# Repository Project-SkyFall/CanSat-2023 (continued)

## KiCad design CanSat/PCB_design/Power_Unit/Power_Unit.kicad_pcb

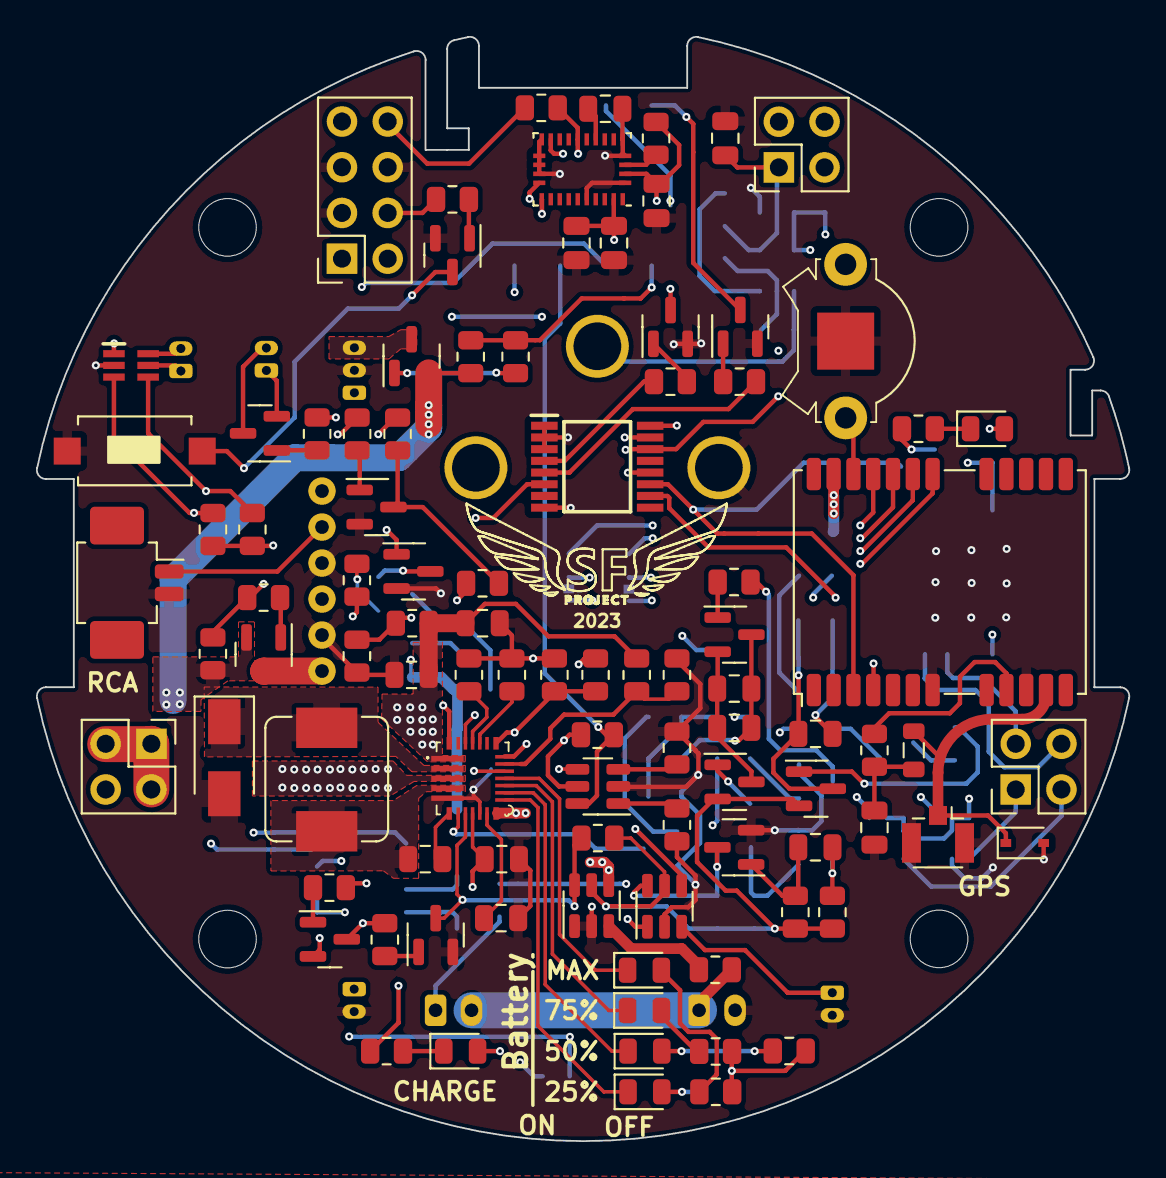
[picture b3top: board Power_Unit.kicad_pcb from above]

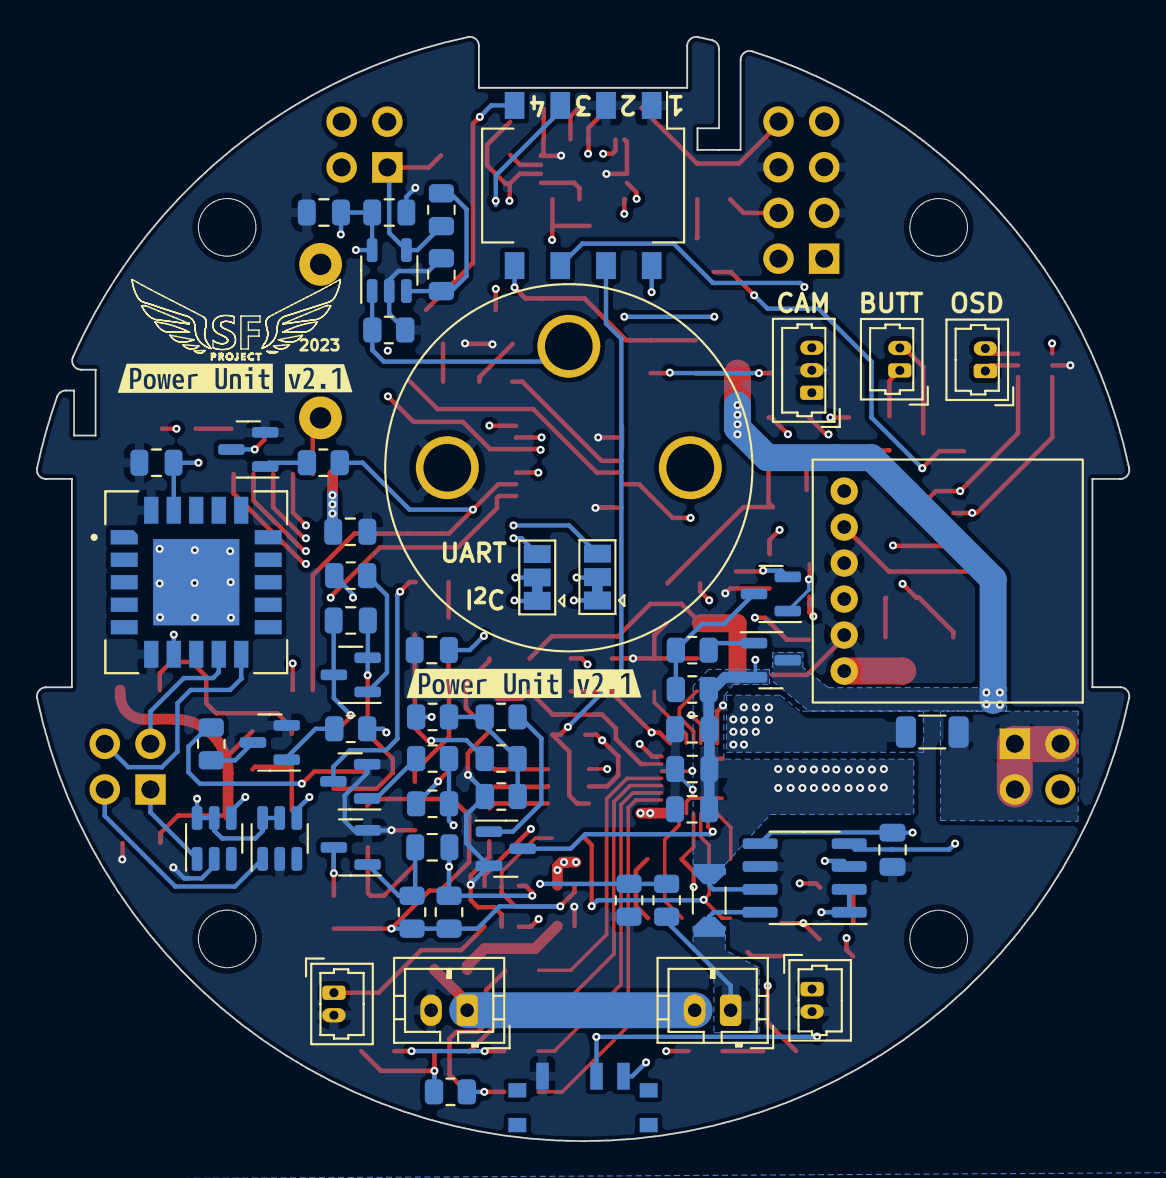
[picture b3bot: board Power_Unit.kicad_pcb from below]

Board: 4 copper layers, 60.7 x 61.3 mm, 162 parts (63 on the bottom side), 119 nets.

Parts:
AE1001: Antenna_Shield; U.FL_Hirose_U.FL-R-SMT-1_Vertical
BT301, BT302: Battery_Cell; JST_PH_B2B-PH-K_1x02_P2.00mm_Vertical
BT1001: Backup battery; 2989
C201, C401, C1102, C1204: 10uF; C_0805_2012Metric
C301, C302, C701, C702, C707, C1201, C1202: 22uF; C_0805_2012Metric
C703, C706, C1001: 1uF; C_0805_2012Metric
C704, C705, C803, C804, C901, C1002, C1101: 0.1uF; C_0805_2012Metric
C708: 4.7uF; C_0805_2012Metric
C801: 120nF; C_0805_2012Metric
C802: 6.8nF; C_0805_2012Metric
C1103: 10nF; C_0805_2012Metric
C1203: NC; C_0805_2012Metric
D701: B330A; D_SMA
D702, D703, D704, D705: APT2012LZGCK; LED_0805_2012Metric
D706: APT2012LSECK/J3-PRV; LED_0805_2012Metric
D1001: APT2012LSECK/J4-PRV; LED_0805_2012Metric
D1002: ESD7351HT1G; D_SOD-323
H201, H202, H203, H204: MountingHole; MountingHole_3.2mm_M3
J101: Conn_02x04_Female; PinSocket_2x04_P2.54mm_Vertical
J102, J103, J104: Conn_02x02_Female; PinSocket_2x02_P2.54mm_Vertical
J501: Conn_01x02; Molex_PicoBlade_53261-0271_1x02-1MP_P1.25mm_Horizontal
J502: Conn_01x03; Molex_PicoBlade_53047-0310_1x03_P1.25mm_Vertical
J503, J504: Conn_01x02; Molex_PicoBlade_53047-0210_1x02_P1.25mm_Vertical
JP1001, JP1002: SolderJumper_3_Bridged12; SolderJumper-3_P1.3mm_Bridged12_Pad1.0x1.5mm
L701: SRP7050AA-2R2M; L_Bourns_SRP7050AA
L1001: 27nH; L_0805_2012Metric
Q201, Q202, Q203, Q207, Q209, Q210, Q211, Q212, Q301, Q302, Q501, Q1001, Q1202, Q1205: BC847; SOT-23
Q204, Q205, Q206: SI2305CDS-T1-BE3; SOT-23
Q208, Q1201, Q1203, Q1204, Q1206: BC857; SOT-23
R201, R202, R204, R207, R208, R209, R1201, R1202, R1203, R1204, R1205, R1206, R1209: 100k; R_0805_2012Metric
R203, R205, R206, R210, R214, R215, R220, R221, R222, R301, R304, R703, R716, R718, R801, R802, R1207: 10k; R_0805_2012Metric
R211: 12k; R_0805_2012Metric
R212, R216, R217, R218, R219, R501, R1001: 5k; R_0805_2012Metric
R213: 0R; R_1206_3216Metric
R302, R303: 220k; R_0805_2012Metric
R401: PE1206FRE470R04L; R_1206_Current
R701: 0R5; R_0805_2012Metric
R702: 3k16; R_0805_2012Metric
R704: 1k87; R_0805_2012Metric
R705: 1k3; R_0805_2012Metric
R706: 5k11; R_0805_2012Metric
R707, R708, R709, R710: 910R; R_0805_2012Metric
R712: 143k; R_0805_2012Metric
R713: 82k; R_0805_2012Metric
R714: 820k; R_0805_2012Metric
R715: 75k; R_0805_2012Metric
R717: 27k4; R_0805_2012Metric
R1002: 750R; R_0805_2012Metric
R1003: 10R; R_0805_2012Metric
R1101, R1102: 100R; R_0805_2012Metric
R1103: 20k; R_0805_2012Metric
R1208: 15k; R_0805_2012Metric
SW201: DS04-254-1-04BK-SMT; SW_DIP_SPSTx04_Slide_Omron_A6S-410x_W8.9mm_P2.54mm
SW202: PCM12SMTR
SW203: LaskaKit tlačítko; Tlačítko SMD LaskaKit
TH301, TH302: NRBE104J3435B2J; Molex_PicoBlade_53047-0210_1x02_P1.25mm_Vertical
U201: PCA8574PW; SOP65P640X110-16N
U301, U701, U703, U1002, U1003: TS5A3159DBV; SOT-23-6
U401: INA219AxD; SOIC-8_3.9x4.9mm_P1.27mm
U501: AD5246BKSZ100; SOT65P210X110-6N
U601: TBS_UNIFY_PRO32_5G8_nano; TBS UNIFY PRO32 5G8 nano
U702: MP2639AGR-Z; MP2639AGRZ
U801: BNO055; LGA-28_5.2x3.8mm_P0.5mm
U901: SCD41; XDCR_SCD41-D-R2
U1001: NEO-M9N; ublox_NEO
U1101: ME2-02; ME2-O2
U1102: MCP6486UT-E/OT; SOT-23-5
kibuzzard-63BEDE70, kibuzzard-63BEDE70#2: G***; kibuzzard-63BEDE70
kibuzzard-642811A6: G***; kibuzzard-642811A6
kibuzzard-642811B8: G***; kibuzzard-642811B8

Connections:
/Power Unit/BATT_INT: J101.4, R217.2
/Power Unit/BAT_SENSE: C201.1, J102.2, R211.2, R212.1
/Power Unit/Battery Pack/BAT_M: BT301.2 (-), BT302.1 (+), R701.2
/Power Unit/Battery Pack/NTC: R704.1, R706.1, U301.4, U702.20 (NTC)
/Power Unit/Battery Pack/NTC_SWITCH: C301.1, Q301.3 (C), R301.1, U301.6
/Power Unit/CAMTRANS-FET: Q204.2 (S), Q205.3 (D), Q206.2 (S), R208.2, R209.1
/Power Unit/CAM_CONTROL: R501.1, U201.6 (P2)
/Power Unit/CH_SLOW/FAST: R716.2, SW201.7, U703.6
/Power Unit/Camera transmit/VIDEO: J501.1, J502.1, U601.5 (Video)
/Power Unit/Camera transmit/V_IN: Q206.3 (D), U601.1 (V_{IN})
/Power Unit/Camera/V_IN: J502.3, Q204.3 (D)
/Power Unit/D delay/OUT: R220.2, R1207.2, R1208.2, R1209.2
/Power Unit/EXTINT_{GPS}: U201.10 (P5), U1001.4 (EXTINT)
/Power Unit/FPV_{SM_A}: J101.2, U601.6 (SA)
/Power Unit/GND: AE1001.2 (Shield), BT302.2 (-), BT1001.2 (-), C201.2, C401.1, C701.2, C702.2, C703.2, C705.2, C706.2, C707.2, C708.2, C801.2, C802.2, C803.2, C804.2, C901.2, C1001.1, C1002.1, C1101.2, C1102.2, C1103.2, D701.2 (A), D1002.2 (A), J101.3, J101.5, J101.6, J501.2, J502.2, Q201.2 (E), Q203.2 (E), Q207.2 (E), Q209.2 (E), Q210.2 (E), Q211.2 (E), Q212.2 (E), Q301.2 (E), Q302.2 (E), Q1001.2 (E), Q1202.2 (E), Q1205.2 (E), R212.2, R702.2, R706.2, R712.2, R713.2, R714.2, R715.2, R718.2, R1101.2, R1102.1, R1209.1, SW201.1, SW201.2, SW202.1 (A), SW203.1, TH301.2, TH302.2, U201.1 (A0), U201.2 (A1), U201.3 (A2), U201.8 (VSS), U301.2 (GND), U401.6 (GND), U501.2 (VSS), U601.2 (GND), U601.4 (GND), U701.1, U701.2 (GND), U702.5 (PGND), U702.10 (AGND), U703.2 (GND), U801.2 (GND), U801.5 (PS1), U801.6 (PS0), U801.15 (GNDIO), U801.16 (GNDIO), U801.17 (COM3), U801.18 (COM2), U801.25 (GNDIO), U901.6 (GND), U901.20 (GND), U901.21 (GND), U1001.7 (VDD_USB), U1001.10 (GND), U1002.2 (GND), U1003.2 (GND), U1101.1 (OUT-), U1102.2 (V-)
/Power Unit/IMU_{INT}: J102.4, U801.14 (INT)
/Power Unit/IS_CHARGE: Q208.3 (C), R201.1, R215.1
/Power Unit/IS_USB: J101.1, Q208.2 (E)
/Power Unit/M_SWITCH: J104.4, R204.1, R1201.1, R1202.1, R1205.1, R1206.1, SW202.2 (B)
/Power Unit/OXY_{OUT}: C1103.1, J102.1, R1103.2, U1102.4
/Power Unit/P_IN: BT301.1 (+), R211.1, R401.1, U401.8 (IN+)
/Power Unit/P_OUT: C701.1, C702.1, C703.1, Q205.2 (S), R202.2, R207.1, R401.2, U401.7 (IN-), U702.3 (VH)
/Power Unit/RESET_{IMU}: R802.2, U201.12 (P7), U801.11 (~RESET)
/Power Unit/SCL: J103.3, R221.2, U201.14 (SCL), U401.4 (SCL), U501.3 (SCL), U801.19 (COM1), U901.9 (SCL)
/Power Unit/SCL_{2}/TXD: J103.2, U1003.1
/Power Unit/SDA: J103.4, R222.2, U201.15 (SDA), U401.3 (SDA), U501.4 (SDA), U801.20 (COM0), U901.10 (SDA)
/Power Unit/SDA_{2}/RXD: J103.1, U1002.1
/Power Unit/SW_CAMERA: R206.2, R209.2, SW201.5
/Power Unit/SW_CAMERA_{IO}: R218.2, U201.4 (P0)
/Power Unit/SW_CHARGE: R216.1, SW201.8
/Power Unit/SW_TRANSMIT: R208.1, R210.1, SW201.6
/Power Unit/SW_TRANSMIT_{IO}: R219.2, U201.5 (P1)
/Power Unit/Switch-mode battery charger/BST: C704.2, U702.6 (BST)
/Power Unit/Switch-mode battery charger/FB: R702.1, R703.2, U702.17 (FB)
/Power Unit/Switch-mode battery charger/ILIM: U702.24 (ILIM), U703.4
/Power Unit/Switch-mode battery charger/ISET: R712.1, U702.23 (ISET)
/Power Unit/Switch-mode battery charger/LX: D701.1 (K), L701.2, U702.2 (LX)
/Power Unit/Switch-mode battery charger/MODE: Q207.3 (C), R214.2, U701.6, U702.8 (MODE)
/Power Unit/Switch-mode battery charger/OLIM: R715.1, U702.22 (OLIM)
/Power Unit/Switch-mode battery charger/SW: C704.1, L701.1, U702.4 (SW)
/Power Unit/Switch-mode battery charger/TMR: C705.1, U702.11 (TMR)
/Power Unit/Switch-mode battery charger/VL: C707.1, C708.1, R213.2, R703.1, R717.1, U702.1 (VL)
/Power Unit/Switch-mode battery charger/VLIM: R717.2, R718.1, U702.18 (VLIM)
/Power Unit/Switch-mode battery charger/VNTC: D706.2 (A), R704.2, R707.1, R708.1, R709.1, R710.1, U702.19 (VNTC)
/Power Unit/Switch-mode battery charger/~CHG: R705.2, U702.26 (~CHG)
/Power Unit/Switch-mode battery charger/~PB: Q209.3 (C), Q212.3 (C), SW203.2, U702.7 (~PB)
/Power Unit/TIMEPULSE_{GPS}: R1001.1, U201.11 (P6), U1001.3 (TIMEPULSE)
/Power Unit/VCC: C401.2, C801.1, C802.1, C803.1, C901.1, C1001.2, C1101.1, C1102.1, D1001.2 (A), J101.7, J101.8, J102.3, R221.1, R222.1, R801.2, R802.1, U201.16 (VDD), U401.1 (A1), U401.2 (A0), U401.5 (VS), U501.1 (VDD), U801.3 (VDD), U801.28 (VDDIO), U901.7 (VDD), U901.19 (VDDH), U1001.23 (VCC), U1002.5 (V+), U1002.6, U1003.5 (V+), U1003.6, U1102.5 (V+)
/Power Unit/VCC_5V: J104.1, J104.2, J104.3, R213.1
/Power Unit/VCC_{BCK}: C706.1, Q1201.2 (E), Q1204.2 (E), R214.1, R301.2, R302.2, R303.2, R304.2, R716.1, SW202.3 (C), U301.5 (V+), U701.5 (V+), U702.9 (VCC), U703.5 (V+)
unnamed: AE1001.1 (A), D1002.1 (K), L1001.2, U1001.11 (RF_IN)
unnamed: BT1001.1 (+), U1001.22 (V_BCKP)
unnamed: C301.2, Q302.1 (B), R302.1
unnamed: C302.1, Q301.1 (B), R303.1
unnamed: C302.2, Q302.3 (C), R304.1
unnamed: C804.1, U801.9 (CAP)
unnamed: C1002.2, L1001.1, R1003.1
unnamed: C1201.1, C1202.1, Q1201.3 (C), Q1203.2 (E)
unnamed: C1201.2, C1202.2, Q1203.3 (C), R1208.1
unnamed: C1203.1, C1204.1, Q1204.3 (C), Q1206.2 (E)
unnamed: C1203.2, C1204.2, Q1206.3 (C), R1207.1
unnamed: D702.1 (K), U702.13 (LED1)
unnamed: D702.2 (A), R710.2
unnamed: D703.1 (K), U702.14 (LED2)
unnamed: D703.2 (A), R707.2
unnamed: D704.1 (K), U702.15 (LED3)
unnamed: D704.2 (A), R708.2
unnamed: D705.1 (K), U702.16 (LED4)
unnamed: D705.2 (A), R709.2
unnamed: D706.1 (K), R705.1
unnamed: D1001.1 (K), R1002.1
unnamed: J503.1, Q501.2 (E)
unnamed: J503.2, Q501.3 (C)
unnamed: J504.1, U501.5 (B)
unnamed: J504.2, U501.6 (W)
unnamed: JP1001.1 (A), U1001.18 (SDA/~SPI_CS)
unnamed: JP1001.2 (C), U1002.4
unnamed: JP1001.3 (B), U1001.20 (TXD/SPI_MISO)
unnamed: JP1002.1 (A), U1001.19 (SCL/SPI_CLK)
unnamed: JP1002.2 (C), U1003.4
unnamed: JP1002.3 (B), U1001.21 (RXD/SPI_MOSI)
unnamed: Q201.1 (B), R201.2
unnamed: Q201.3 (C), R202.1, R203.1
unnamed: Q202.1 (B), R204.2
unnamed: Q202.2 (E), Q203.3 (C)
unnamed: Q202.3 (C), R205.2, R207.2
unnamed: Q203.1 (B), R203.2
unnamed: Q204.1 (G), R206.1
unnamed: Q205.1 (G), R205.1
unnamed: Q206.1 (G), R210.2
unnamed: Q207.1 (B), R215.2
unnamed: Q208.1 (B), R216.2
unnamed: Q209.1 (B), R217.1
unnamed: Q210.1 (B), R218.1
unnamed: Q210.3 (C), SW201.3
unnamed: Q211.1 (B), R219.1
unnamed: Q211.3 (C), SW201.4
unnamed: Q212.1 (B), R220.1
unnamed: Q501.1 (B), R501.2
unnamed: Q1001.1 (B), R1001.2
unnamed: Q1001.3 (C), R1002.2
unnamed: Q1201.1 (B), R1201.2
unnamed: Q1202.1 (B), R1202.2
unnamed: Q1202.3 (C), R1203.1
unnamed: Q1203.1 (B), R1203.2
unnamed: Q1204.1 (B), R1204.2
unnamed: Q1205.1 (B), R1205.2
unnamed: Q1205.3 (C), R1204.1
unnamed: Q1206.1 (B), R1206.2
unnamed: R701.1, U701.3
unnamed: R713.1, U703.3
unnamed: R714.1, U703.1
unnamed: R801.1, U801.4 (~BOOT_LOAD_PIN)
unnamed: R1003.2, U1001.9 (VCC_RF)
unnamed: R1101.1, U1101.2 (OUT), U1102.1 (+)
unnamed: R1102.2, R1103.1, U1102.3 (-)
unnamed: TH301.1, U301.1
unnamed: TH302.1, U301.3
unnamed: U701.4, U702.12 (MIND)

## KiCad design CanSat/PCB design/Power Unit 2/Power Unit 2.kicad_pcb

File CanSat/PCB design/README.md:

# PCB design
## Content
* ### [Disclaimer](#disclaimer-1)
* ### [Power Unit](#power-unit-1)

## Disclaimer
PCBs designed in KiCad

## Power Unit
### Description
Power Unit is base PCB from stackup. It charges batteries or supplies rest of CanSat with 5 V power.
### Used ICs
#### MP2639A
* Balances 2s Li-po batteries and charges them from USB
* Overvoltage, overcurrent and overtemperature battery protection
* Step-down battery voltage to 5 V

## Control Unit
### Description

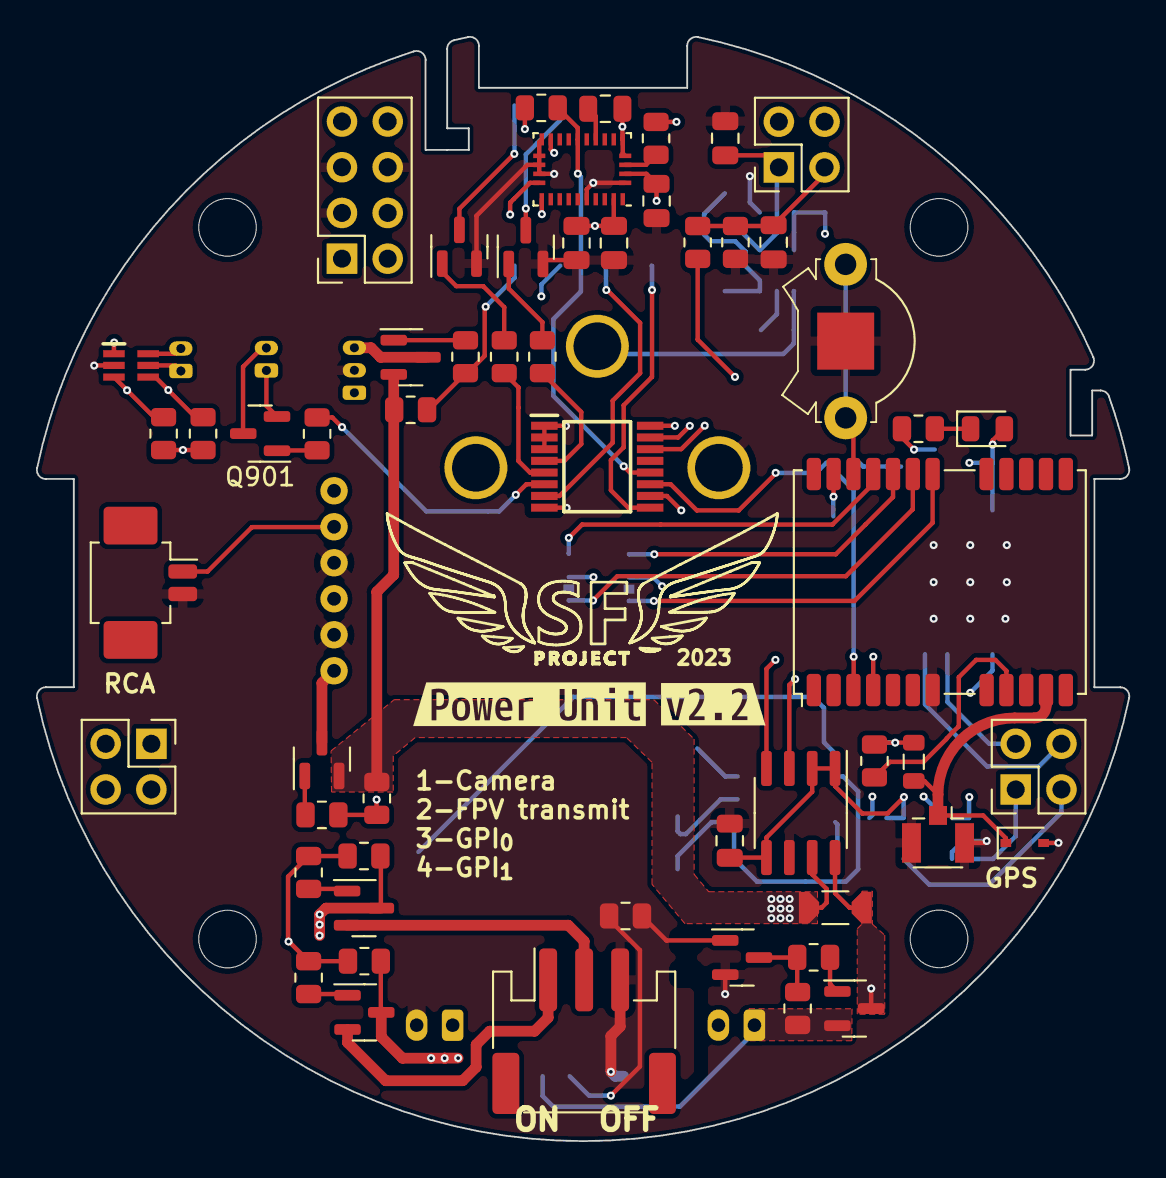
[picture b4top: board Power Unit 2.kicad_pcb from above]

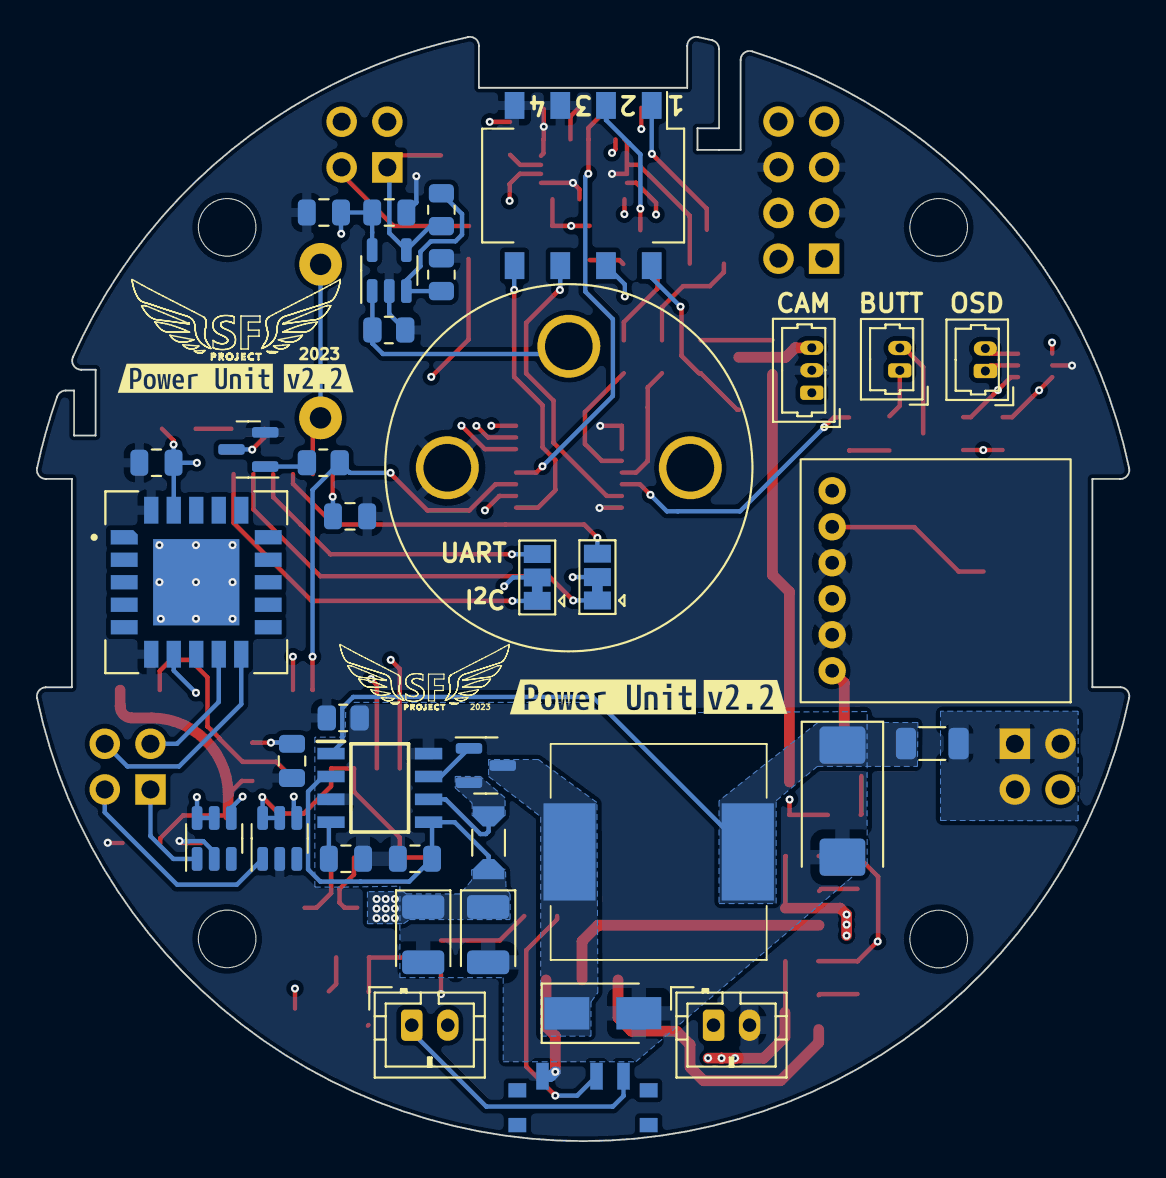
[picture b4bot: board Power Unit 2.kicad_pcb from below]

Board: 4 copper layers, 60.7 x 61.3 mm, 102 parts (41 on the bottom side), 70 nets.

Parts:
AE601: Antenna_Shield; U.FL_Hirose_U.FL-R-SMT-1_Vertical
BT201, BT202: Battery_Cell; JST_PH_B2B-PH-K_1x02_P2.00mm_Vertical
BT601: Backup battery; 2989
C201, C401, C802: 10uF; C_0805_2012Metric
C301, C503, C504, C602, C701, C801: 0.1uF; C_0805_2012Metric
C302, C303: TPSB686K010R0600; CP_EIA-3528-21_Kemet-B
C304: 0.47uF; C_0805_2012Metric
C305: 293D227X9010D2TE3; CP_EIA-7343-31_Kemet-D
C501: 120nF; C_0805_2012Metric
C502: 6.8nF; C_0805_2012Metric
C601: 1uF; C_0805_2012Metric
C803: 10nF; C_0805_2012Metric
D301: B330A; D_SMA
D601: APT2012LSECK/J4-PRV; LED_0805_2012Metric
D602: ESD7351HT1G; D_SOD-323
H201, H202, H203, H204: MountingHole; MountingHole_3.2mm_M3
IC301: MAX1626ESA+T; SOIC127P600X175-8N
J101: Conn_02x04_Female; PinSocket_2x04_P2.54mm_Vertical
J102, J103, J104: Conn_02x02_Female; PinSocket_2x02_P2.54mm_Vertical
J201: Conn_01x03; JST_PH_S3B-PH-SM4-TB_1x03-1MP_P2.00mm_Horizontal
J901: Conn_01x02; Molex_PicoBlade_53261-0271_1x02-1MP_P1.25mm_Horizontal
J902: Conn_01x03; Molex_PicoBlade_53047-0310_1x03_P1.25mm_Vertical
J903, J904: Conn_01x02; Molex_PicoBlade_53047-0210_1x02_P1.25mm_Vertical
JP601, JP602: SolderJumper_3_Bridged12; SolderJumper-3_P1.3mm_Bridged12_Pad1.0x1.5mm
L301: CDRH125NP-220MC; CDRH125101MC
L601: 27nH; L_0805_2012Metric
Q201, Q202, Q204, Q205, Q206, Q301: SI2305CDS-T1-BE3; SOT-23
Q203, Q207, Q208, Q601: BC847; SOT-23
Q901: BC857; SOT-23
R201, R202, R207, R210, R213, R218, R219, R501, R502: 10k; R_0805_2012Metric
R203, R204, R205, R206, R211, R212: 100k; R_0805_2012Metric
R208: 12k; R_0805_2012Metric
R209, R216, R217, R601, R901: 5k; R_0805_2012Metric
R214: 0R; R_0805_2012Metric
R215: 0R; R_1206_3216Metric
R301, R401: PE1206FRE470R04L; R_1206_Current
R602: 750R; R_0805_2012Metric
R603: 10R; R_0805_2012Metric
R801, R802: 100R; R_0805_2012Metric
R803: 20k; R_0805_2012Metric
SW201: DS04-254-1-04BK-SMT; SW_DIP_SPSTx04_Slide_Omron_A6S-410x_W8.9mm_P2.54mm
SW202: PCM12SMTR
U201: PCA8574PW; SOP65P640X110-16N
U401: INA219AxD; SOIC-8_3.9x4.9mm_P1.27mm
U501: BNO055; LGA-28_5.2x3.8mm_P0.5mm
U601, U602: TS5A3159DBV; SOT-23-6
U603: NEO-M9N; ublox_NEO
U701: SCD41; XDCR_SCD41-D-R2
U801: ME2-02; ME2-O2
U802: MCP6486UT-E/OT; SOT-23-5
U901: AD5246BKSZ100; SOT65P210X110-6N
U1001: TBS_UNIFY_PRO32_5G8_nano; TBS UNIFY PRO32 5G8 nano
kibuzzard-63BEDE70: G***; kibuzzard-63BEDE70
kibuzzard-642731D3: G***; kibuzzard-642731D3
kibuzzard-642753A9: G***; kibuzzard-642753A9
kibuzzard-642757A1: G***; kibuzzard-642757A1
kibuzzard-64275393: G***; kibuzzard-64275393
kibuzzard-64275791: G***; kibuzzard-64275791

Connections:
/Power Unit/BATT: BT201.1 (+), Q201.3 (D), Q204.2 (S), R203.2, R206.2, SW202.3 (C)
/Power Unit/BAT_SENSE: C201.1, J102.2, R208.2, R209.1
/Power Unit/CAMTRANS-FET: C302.1, C303.1, C304.1, IC301.2 (~_3/5), IC301.5 (V+), Q205.2 (S), Q206.2 (S), R211.2, R212.1, R301.1, R401.2, U401.7 (IN-)
/Power Unit/CAM_CONTROL: R901.1, U201.6 (P2)
/Power Unit/Camera transmit/VIDEO: J901.1, J902.1, U1001.5 (Video)
/Power Unit/Camera transmit/V_IN: Q206.3 (D), U1001.1 (V_{IN})
/Power Unit/Camera/V_IN: J902.3, Q205.3 (D)
/Power Unit/Current Sensor/P_IN: Q204.3 (D), R208.1, R401.1, U401.8 (IN+)
/Power Unit/EXTINT_{GPS}: U201.10 (P5), U603.4 (EXTINT)
/Power Unit/FPV_{SM_A}: J101.2, U1001.6 (SA)
/Power Unit/GND: AE601.2 (Shield), BT202.2 (-), BT601.2 (-), C201.2, C401.1, C501.2, C502.2, C503.2, C504.2, C601.1, C602.1, C701.2, C801.2, C802.2, C803.2, D602.2 (A), J101.3, J101.5, J101.6, J201.3, J901.2, J902.2, Q203.2 (E), Q207.2 (E), Q208.2 (E), Q601.2 (E), R209.2, R214.2, R801.2, R802.1, SW201.3, SW201.4, SW202.1 (A), U201.1 (A0), U201.2 (A1), U201.3 (A2), U201.8 (VSS), U401.6 (GND), U501.2 (GND), U501.5 (PS1), U501.6 (PS0), U501.15 (GNDIO), U501.16 (GNDIO), U501.17 (COM3), U501.18 (COM2), U501.25 (GNDIO), U601.2 (GND), U602.2 (GND), U603.7 (VDD_USB), U603.10 (GND), U701.6 (GND), U701.20 (GND), U701.21 (GND), U801.1 (OUT-), U802.2 (V-), U901.2 (VSS), U1001.2 (GND), U1001.4 (GND)
/Power Unit/GPI_{0}: SW201.6, U201.7 (P3)
/Power Unit/GPI_{1}: SW201.5, U201.9 (P4)
/Power Unit/IMU_{INT}: J102.4, U501.14 (INT)
/Power Unit/M_SWITCH: J104.4, R201.1, R202.1, R203.1, R204.1, R205.1, SW202.2 (B)
/Power Unit/OXY_{OUT}: C803.1, J102.1, R803.2, U802.4
/Power Unit/RESET_{IMU}: R502.2, U201.12 (P7), U501.11 (~RESET)
/Power Unit/SCL: J103.3, R218.2, U201.14 (SCL), U401.4 (SCL), U501.19 (COM1), U701.9 (SCL), U901.3 (SCL)
/Power Unit/SCL_{2}/TXD: J103.2, U602.1
/Power Unit/SDA: J103.4, R219.2, U201.15 (SDA), U401.3 (SDA), U501.20 (COM0), U701.10 (SDA), U901.4 (SDA)
/Power Unit/SDA_{2}/RXD: J103.1, U601.1
/Power Unit/SW_CAMERA: R210.2, R212.2, SW201.8
/Power Unit/SW_CAMERA_{IO}: R217.2, U201.5 (P1)
/Power Unit/SW_TRANSMIT: R211.1, R213.1, SW201.7
/Power Unit/SW_TRANSMIT_{IO}: R216.2, U201.4 (P0)
/Power Unit/Step-down/GND: C301.2, C302.2, C303.2, C304.2, C305.2, D301.2 (A), IC301.3 (SHDN), IC301.8 (GND), R214.1
/Power Unit/Step-down/L_MOSFET: IC301.6 (CS), Q301.2 (S), R301.2
/Power Unit/Step-down/L_{SWITCH}: D301.1 (K), L301.1, Q301.3 (D)
/Power Unit/Step-down/VCC_5V: C305.1, IC301.1 (OUT), L301.2, R215.2
/Power Unit/TIMEPULSE_{GPS}: R601.1, U201.11 (P6), U603.3 (TIMEPULSE)
/Power Unit/VCC: C401.2, C501.1, C502.1, C503.1, C601.2, C701.1, C801.1, C802.1, D601.2 (A), J101.7, J101.8, J102.3, R218.1, R219.1, R501.2, R502.1, U201.16 (VDD), U401.1 (A1), U401.2 (A0), U401.5 (VS), U501.3 (VDD), U501.28 (VDDIO), U601.5 (V+), U601.6, U602.5 (V+), U602.6, U603.23 (VCC), U701.7 (VDD), U701.19 (VDDH), U802.5 (V+), U901.1 (VDD)
/Power Unit/VCC_5V: J104.1, J104.2, J104.3, R215.1
unnamed: AE601.1 (A), D602.1 (K), L601.2, U603.11 (RF_IN)
unnamed: BT201.2 (-), BT202.1 (+), Q202.3 (D), R204.2
unnamed: BT601.1 (+), U603.22 (V_BCKP)
unnamed: C301.1, IC301.4 (REF)
unnamed: C504.1, U501.9 (CAP)
unnamed: C602.2, L601.1, R603.1
unnamed: D601.1 (K), R602.1
unnamed: IC301.7 (EXT), Q301.1 (G)
unnamed: J201.1, Q201.2 (S)
unnamed: J201.2, Q202.2 (S)
unnamed: J904.1, U901.5 (B)
unnamed: J904.2, U901.6 (W)
unnamed: JP601.1 (A), U603.18 (SDA/~SPI_CS)
unnamed: JP601.2 (C), U601.4
unnamed: JP601.3 (B), U603.20 (TXD/SPI_MISO)
unnamed: JP602.1 (A), U603.19 (SCL/SPI_CLK)
unnamed: JP602.2 (C), U602.4
unnamed: JP602.3 (B), U603.21 (RXD/SPI_MOSI)
unnamed: Q201.1 (G), R201.2
unnamed: Q202.1 (G), R202.2
unnamed: Q203.1 (B), R205.2
unnamed: Q203.3 (C), R206.1, R207.2
unnamed: Q204.1 (G), R207.1
unnamed: Q205.1 (G), R210.1
unnamed: Q206.1 (G), R213.2
unnamed: Q207.1 (B), R216.1
unnamed: Q207.3 (C), SW201.2
unnamed: Q208.3 (C), SW201.1
unnamed: Q601.1 (B), R601.2
unnamed: Q601.3 (C), R602.2
unnamed: J903.1, Q901.2 (E)
unnamed: J903.2, Q901.3 (C)
unnamed: Q208.1 (B), R217.1
unnamed: R501.1, U501.4 (~BOOT_LOAD_PIN)
unnamed: R603.2, U603.9 (VCC_RF)
unnamed: R801.1, U801.2 (OUT), U802.1 (+)
unnamed: R802.2, R803.1, U802.3 (-)
unnamed: Q901.1 (B), R901.2

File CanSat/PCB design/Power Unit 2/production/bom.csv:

Designator,Footprint,Quantity,Value,LCSC Part #
AE601,U.FL_Hirose_U.FL-R-SMT-1_Vertical,1,Antenna_Shield,
"BT201, BT202",JST_PH_B2B-PH-K_1x02_P2.00mm_Vertical,2,Battery_Cell,
BT601,2989,1,Backup battery,
"C201, C401, C802",C_0805_2012Metric,3,10uF,
"C301, C503, C504, C602, C701, C801",C_0805_2012Metric,6,0.1uF,
"C302, C303",CP_EIA-3528-21_Kemet-B,2,TPSB686K010R0600,
C304,C_0805_2012Metric,1,0.47uF,
C305,CP_EIA-7343-31_Kemet-D,1,293D227X9010D2TE3,
C501,C_0805_2012Metric,1,120nF,
C502,C_0805_2012Metric,1,6.8nF,
C601,C_0805_2012Metric,1,1uF,
C803,C_0805_2012Metric,1,10nF,
D301,D_SMA,1,B330A,
D601,LED_0805_2012Metric,1,APT2012LSECK/J4-PRV,
D602,D_SOD-323,1,ESD7351HT1G,
IC301,SOIC127P600X175-8N,1,MAX1626ESA+T,
J101,PinSocket_2x04_P2.54mm_Vertical,1,Conn_02x04_Female,
"J102, J103, J104",PinSocket_2x02_P2.54mm_Vertical,3,Conn_02x02_Female,
J201,JST_PH_B3B-PH-SM4-TB_1x03-1MP_P2.00mm_Vertical,1,Conn_01x03,
J901,Molex_PicoBlade_53261-0271_1x02-1MP_P1.25mm_Horizontal,1,Conn_01x02,
J902,Molex_PicoBlade_53047-0310_1x03_P1.25mm_Vertical,1,Conn_01x03,
"J903, J904",Molex_PicoBlade_53047-0210_1x02_P1.25mm_Vertical,2,Conn_01x02,
"JP601, JP602",SolderJumper-3_P1.3mm_Bridged12_Pad1.0x1.5mm,2,SolderJumper_3_Bridged12,
L301,CDRH125101MC,1,CDRH125NP-220MC,
L601,L_0805_2012Metric,1,27nH,
"Q201, Q202, Q204, Q205, Q206, Q301",SOT-23,6,SI2305CDS-T1-BE3,
"Q203, Q207, Q208, Q601, Q901",SOT-23,5,BC847,
"R201, R202, R207, R210, R213, R218, R219, R501, R502",R_0805_2012Metric,9,10k,
"R203, R204, R205, R206, R211, R212",R_0805_2012Metric,6,100k,
R208,R_0805_2012Metric,1,12k,
"R209, R216, R217, R601, R901",R_0805_2012Metric,5,5k,
R214,R_0805_2012Metric,1,0R,
R215,R_1206_3216Metric,1,0R,
"R301, R401",R_1206_Current,2,PE1206FRE470R04L,
R602,R_0805_2012Metric,1,750R,
R603,R_0805_2012Metric,1,10R,
"R801, R802",R_0805_2012Metric,2,100R,
R803,R_0805_2012Metric,1,20k,
SW201,SW_DIP_SPSTx04_Slide_Omron_A6S-410x_W8.9mm_P2.54mm,1,DS04-254-1-04BK-SMT,
SW202,PCM12SMTR,1,PCM12SMTR,
U1001,TBS UNIFY PRO32 5G8 nano,1,TBS_UNIFY_PRO32_5G8_nano,
U201,SOP65P640X110-16N,1,PCA8574PW,
U401,SOIC-8_3.9x4.9mm_P1.27mm,1,INA219AxD,
U501,LGA-28_5.2x3.8mm_P0.5mm,1,BNO055,
"U601, U602",SOT-23-6,2,TS5A3159DBV,
U603,ublox_NEO,1,NEO-M9N,
U701,XDCR_SCD41-D-R2,1,SCD41,
U801,ME2-O2,1,ME2-02,
U802,SOT-23-5,1,MCP6486UT-E/OT,
U901,SOT65P210X110-6N,1,AD5246BKSZ100,

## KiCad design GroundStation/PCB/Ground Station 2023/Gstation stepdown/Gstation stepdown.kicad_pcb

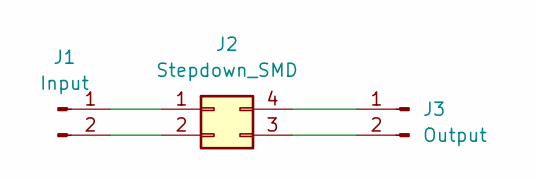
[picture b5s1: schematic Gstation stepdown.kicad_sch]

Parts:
J1: Input; PinHeader_1x02_P2.54mm_Vertical
J2: Stepdown_SMD; StepDown
J3: Output; PinHeader_1x02_P2.54mm_Vertical

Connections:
unnamed: J1.1, J2.1
unnamed: J1.2, J2.2
unnamed: J2.3, J3.2
unnamed: J2.4, J3.1

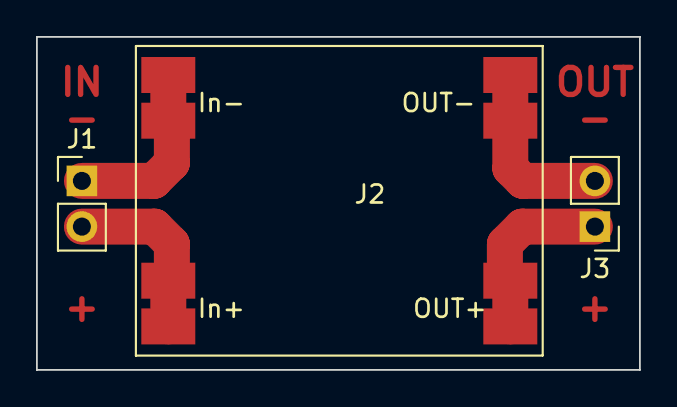
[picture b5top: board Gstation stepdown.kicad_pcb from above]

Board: 2 copper layers, 33.5 x 18.5 mm, 3 parts (0 on the bottom side), 4 nets.

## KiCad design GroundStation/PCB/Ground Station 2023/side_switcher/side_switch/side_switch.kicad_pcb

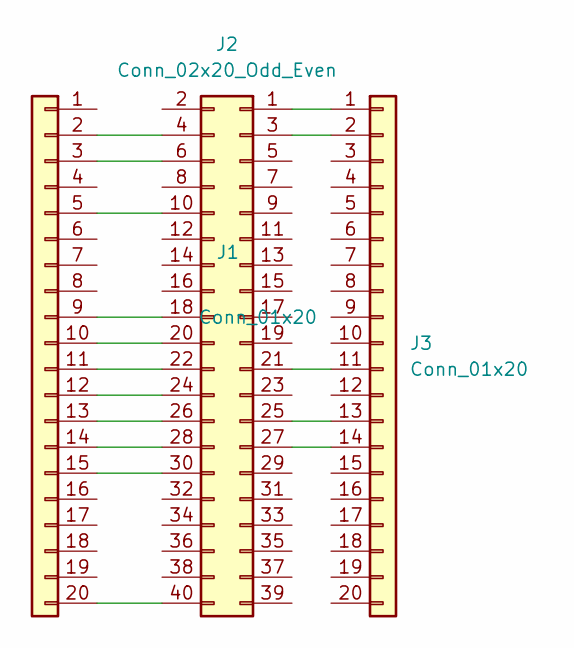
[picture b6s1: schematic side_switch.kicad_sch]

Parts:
J1, J3: Conn_01x20; PinHeader_1x20_P2.54mm_Vertical
J2: Conn_02x20_Odd_Even; PinHeader_2x20_P2.54mm_Vertical

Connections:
unnamed: J1.2, J2.4
unnamed: J1.3, J2.6
unnamed: J1.5, J2.10
unnamed: J1.9, J2.18
unnamed: J1.10, J2.20
unnamed: J1.11, J2.22
unnamed: J1.12, J2.24
unnamed: J1.13, J2.26
unnamed: J1.14, J2.28
unnamed: J1.15, J2.30
unnamed: J1.20, J2.40
unnamed: J2.1, J3.1
unnamed: J2.3, J3.2
unnamed: J2.21, J3.11
unnamed: J2.25, J3.13
unnamed: J2.27, J3.14

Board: 2 copper layers, 3 parts (0 on the bottom side), 16 nets, no tracks yet.

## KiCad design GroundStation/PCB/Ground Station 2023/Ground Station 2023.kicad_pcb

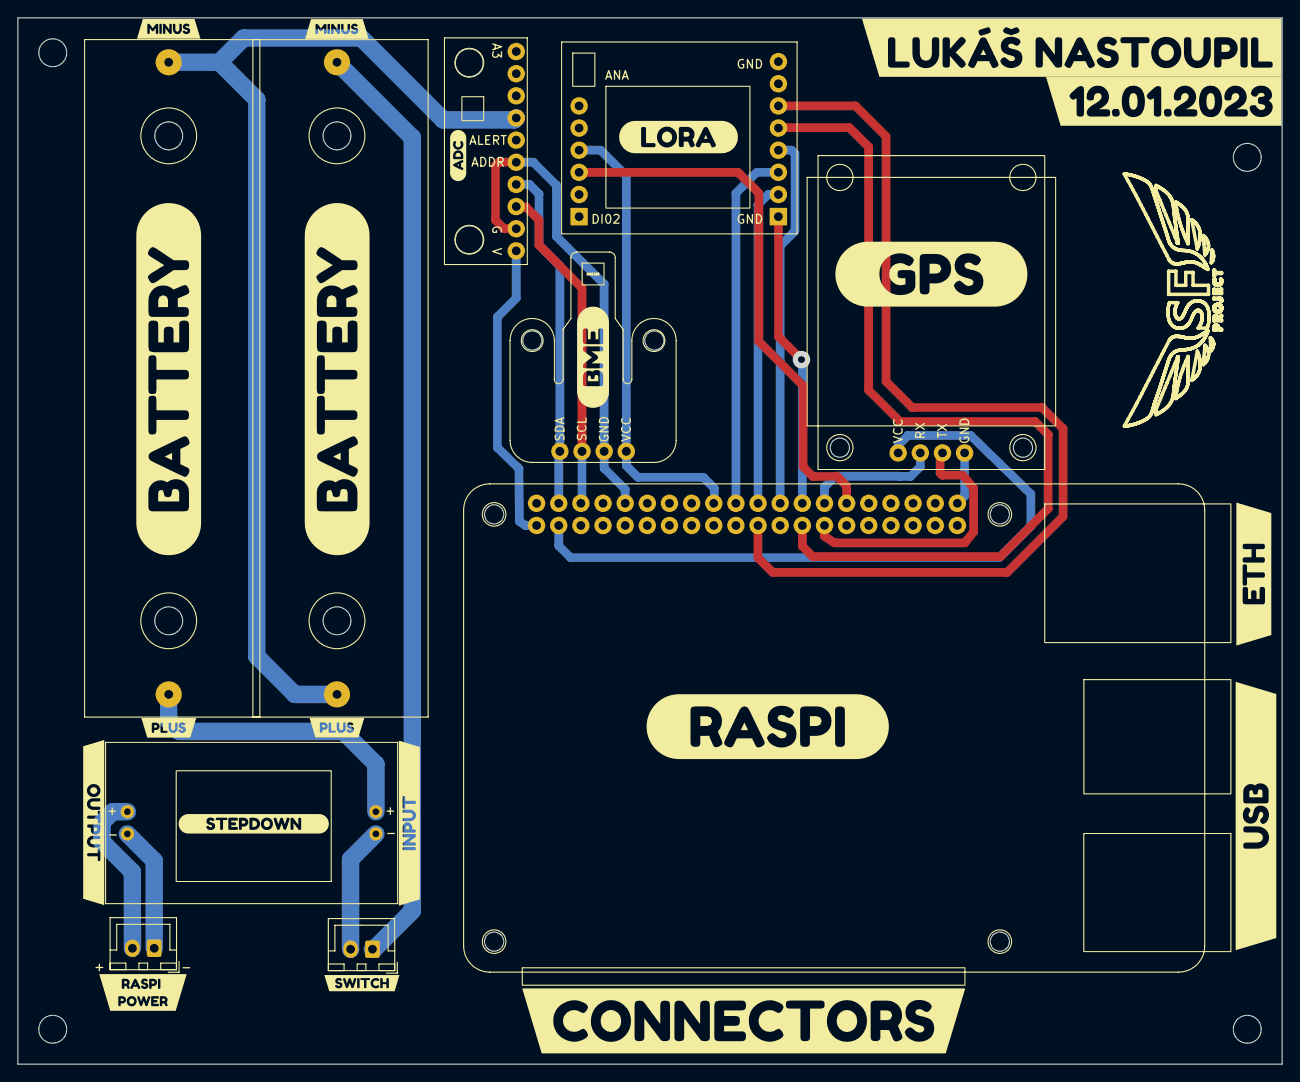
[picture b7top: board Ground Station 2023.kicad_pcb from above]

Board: 2 copper layers, 145.0 x 120.0 mm, 31 parts (0 on the bottom side), 19 nets.

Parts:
ADC1: AD
BME1: BME280
BT1, BT2: Battery_Cell; Battery box
GPS1: GY-NEO6MV2; GPS
LORA1: LORA; Lora deska
RASPI1: Raspberry PI 4B; Raspberry pi 4B
STEPDOWN1: StepDown
SW1: Přepínač; JST_XH_B2B-XH-A_1x02_P2.50mm_Vertical
USB-C1: USB-C; JST_XH_B2B-XH-A_1x02_P2.50mm_Vertical
kibuzzard-63C06CDD: G***; kibuzzard-63C06CDD
kibuzzard-63C07A1A: G***; kibuzzard-63C07A1A
kibuzzard-63C07A12: G***; kibuzzard-63C07A12
kibuzzard-63C07ADB: G***; kibuzzard-63C07ADB
kibuzzard-63C07B39: G***; kibuzzard-63C07B39
kibuzzard-63C07B83: G***; kibuzzard-63C07B83
kibuzzard-63C07C6F: G***; kibuzzard-63C07C6F
kibuzzard-63C07C98: G***; kibuzzard-63C07C98
kibuzzard-63C07CF0: G***; kibuzzard-63C07CF0
kibuzzard-63C07D65: G***; kibuzzard-63C07D65
kibuzzard-63C07E6F: G***; kibuzzard-63C07E6F
kibuzzard-63C07E43: G***; kibuzzard-63C07E43
kibuzzard-63C070CF: G***; kibuzzard-63C070CF
kibuzzard-63C071A1: G***; kibuzzard-63C071A1
kibuzzard-63C072BC: G***; kibuzzard-63C072BC
kibuzzard-63C074B7, kibuzzard-63C074B7#2: G***; kibuzzard-63C074B7
kibuzzard-63C0733F: G***; kibuzzard-63C0733F
kibuzzard-63C0781A: G***; kibuzzard-63C0781A
kibuzzard-63C0785A: G***; kibuzzard-63C0785A
kibuzzard-63C07127: G***; kibuzzard-63C07127

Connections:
+3V3: BME1.4, LORA1.5, RASPI1.1, RASPI1.17
+5V: ADC1.10, GPS1.1, RASPI1.2, RASPI1.4
DI00: LORA1.6, RASPI1.29
GNDD: ADC1.6, ADC1.9, BME1.3, GPS1.4, LORA1.9, LORA1.16, RASPI1.6, RASPI1.9, RASPI1.14, RASPI1.20, RASPI1.25, RASPI1.30, RASPI1.34, RASPI1.39
IN+: BT1.1 (+), STEPDOWN1.2 (Pin_7)
IN-: STEPDOWN1.1, SW1.2 (B)
MISO: LORA1.10, RASPI1.21
MOSI: LORA1.11, RASPI1.19
NSS: LORA1.13, RASPI1.26
unnamed: ADC1.4, BT1.2 (-), BT2.1 (+)
unnamed: BT2.2 (-), SW1.1 (A)
OUT+: STEPDOWN1.4 (Pin_6), USB-C1.2
OUT-: STEPDOWN1.3 (Pin_2), USB-C1.1
RESET: LORA1.14, RASPI1.22
RXD2: GPS1.3, RASPI1.28
SCK: LORA1.12, RASPI1.23
SCL: ADC1.8, BME1.2, RASPI1.5
SDA: ADC1.7, BME1.1, RASPI1.3
TXD2: GPS1.2, RASPI1.27

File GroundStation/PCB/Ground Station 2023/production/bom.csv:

Designator,Footprint,Quantity,Value,LCSC Part #
ADC1,AD,1,AD,
BME1,BME280,1,BME280,
"BT1, BT2",Battery box,2,Battery_Cell,
GPS1,GPS,1,GY-NEO6MV2,
LORA1,Lora deska,1,LORA,
RASPI1,Raspberry pi 4B,1,Raspberry PI 4B,
STEPDOWN1,StepDown,1,StepDown,
SW1,JST_XH_B2B-XH-A_1x02_P2.50mm_Vertical,1,Přepínač,
USB-C1,JST_XH_B2B-XH-A_1x02_P2.50mm_Vertical,1,USB-C,
